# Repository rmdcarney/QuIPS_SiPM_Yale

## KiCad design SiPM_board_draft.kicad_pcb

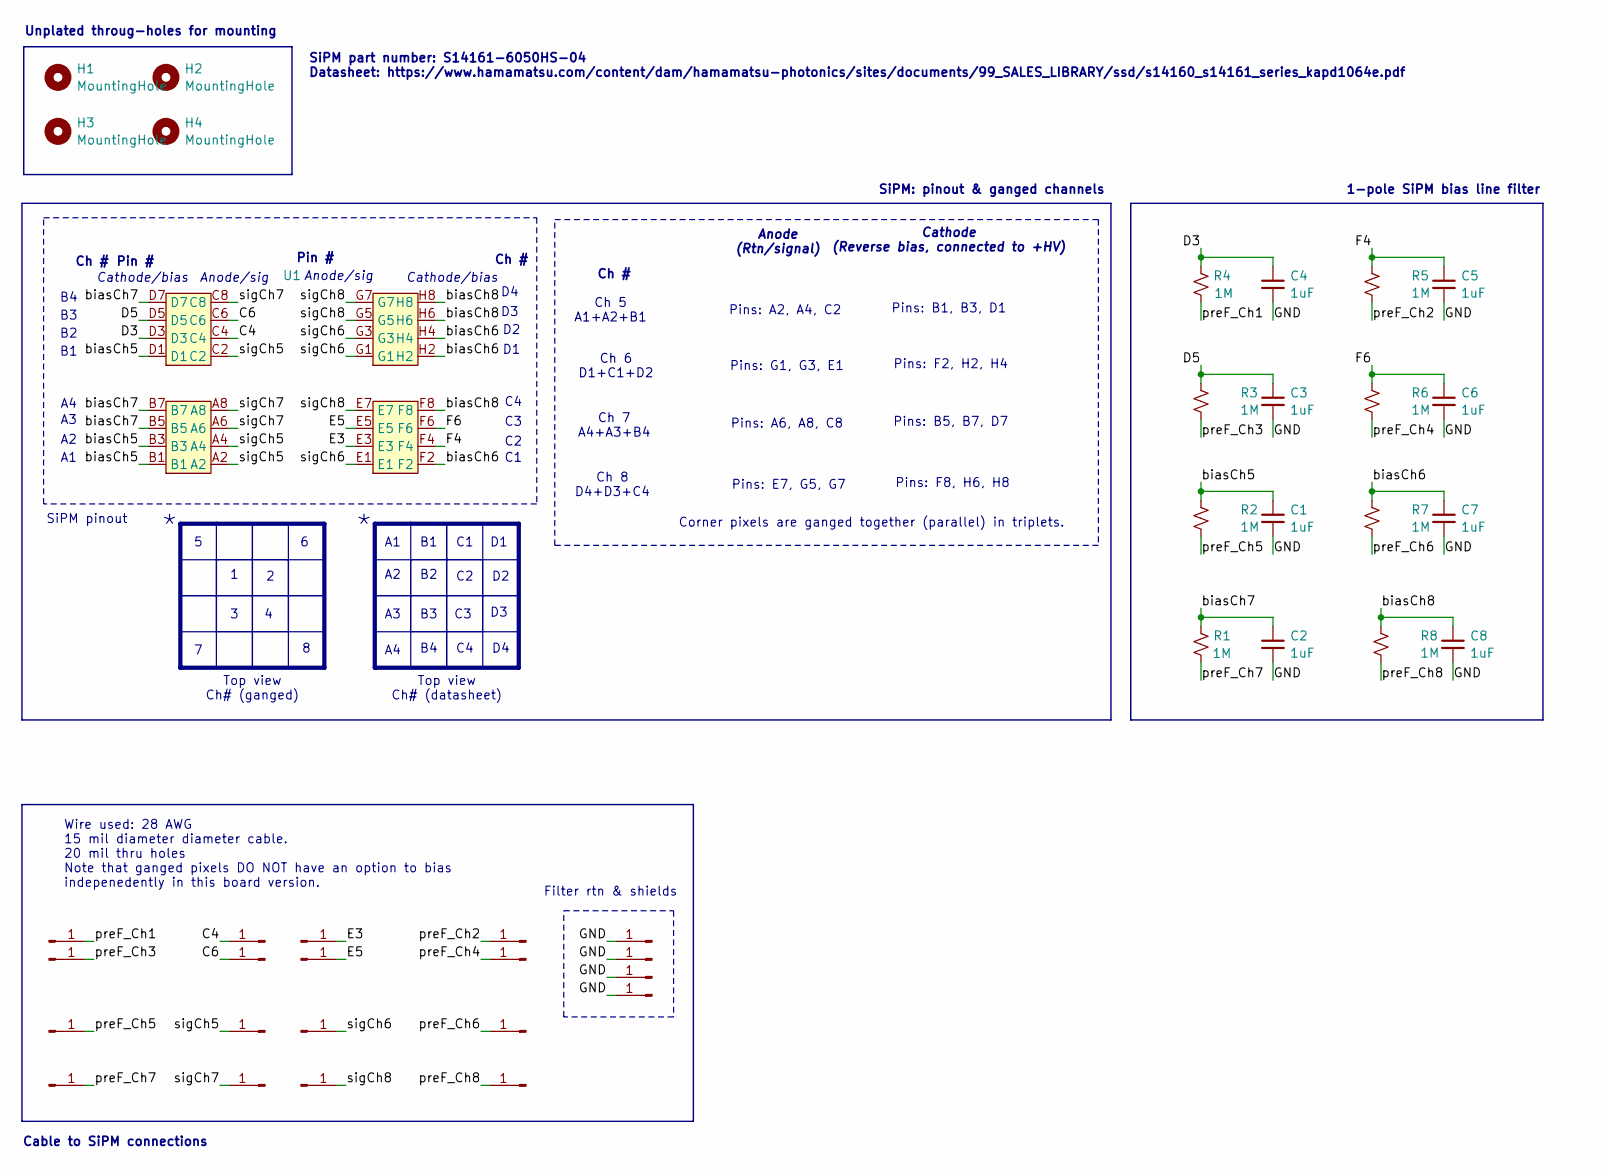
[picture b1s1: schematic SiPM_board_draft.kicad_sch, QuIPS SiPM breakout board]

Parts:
C1, C2, C3, C4, C5, C6, C7, C8: 1uF; C_0805_2012Metric
H1, H2, H3, H4: MountingHole; MountingHole_3.5mm
J1, J2, J3, J4, J5, J7, J8, J10, J11, J12, J13, J16, J18, J19, J21, J24, J26, J27, J29, J32: Conn_01x01_Pin; SolderWire-0.15sqmm_1x01_D0.5mm_OD1.5mm
R1, R2, R3, R4, R5, R6, R7, R8: 1M; R_0402_1005Metric
U1: S14161-6050HS-04_landing

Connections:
/C4: J19.1, U1.C4
/C6: J18.1, U1.C6
/D3: C4.1, R4.1, U1.D3
/D5: C3.1, R3.1, U1.D5
/E3: J10.1, U1.E3
/E5: J11.1, U1.E5
/F4: C5.1, R5.1, U1.F4
/F6: C6.1, R6.1, U1.F6
/GND: C1.2, C2.2, C3.2, C4.2, C5.2, C6.2, C7.2, C8.2, J1.1, J4.1, J7.1, J12.1
/biasCh5: C1.1, R2.1, U1.B1, U1.B3, U1.D1
/biasCh6: C7.1, R7.1, U1.F2, U1.H2, U1.H4
/biasCh7: C2.1, R1.1, U1.B5, U1.B7, U1.D7
/biasCh8: C8.1, R8.1, U1.F8, U1.H6, U1.H8
/preF_Ch1: J2.1, R4.2
/preF_Ch2: J27.1, R5.2
/preF_Ch3: J3.1, R3.2
/preF_Ch4: J26.1, R6.2
/preF_Ch5: J5.1, R2.2
/preF_Ch6: J32.1, R7.2
/preF_Ch7: J8.1, R1.2
/preF_Ch8: J29.1, R8.2
/sigCh5: J24.1, U1.A2, U1.A4, U1.C2
/sigCh6: J13.1, U1.E1, U1.G1, U1.G3
/sigCh7: J21.1, U1.A6, U1.A8, U1.C8
/sigCh8: J16.1, U1.E7, U1.G5, U1.G7

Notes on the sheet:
Top view Ch# (datasheet)
Pins: G1, G3, E1
Cable to SiPM connections
Pins: A6, A8, C8
Anode (Rtn/signal)
Anode/sig
Cathode (Reverse bias, connected to +HV)
Pins: F8, H6, H8
Ch #
1-pole SiPM bias line filter
Pins: B5, B7, D7
Unplated throug-holes for mounting
Pins: A2, A4, C2
Corner pixels are ganged together (parallel) in triplets.
Cathode/bias
SiPM part number: S14161-6050HS-04 Datasheet: https://www.hamamatsu.com/content/dam/hamamatsu-photonics/sites/documents/99_SALES_LIBRARY/ssd/s14160_s14161_series_kapd1064e.pdf
Ch 5 A1+A2+B1
Wire used: 28 AWG 15 mil diameter diameter cable. 20 mil thru holes Note that ganged pixels DO NOT have an option to bias indepenedently in this board version.
Pin #
Ch 6 D1+C1+D2
SiPM pinout
Pins: F2, H2, H4
Pins: B1, B3, D1
Ch 8 D4+D3+C4
SiPM: pinout & ganged channels
Top view Ch# (ganged)
Ch 7 A4+A3+B4
Filter rtn & shields
Pins: E7, G5, G7

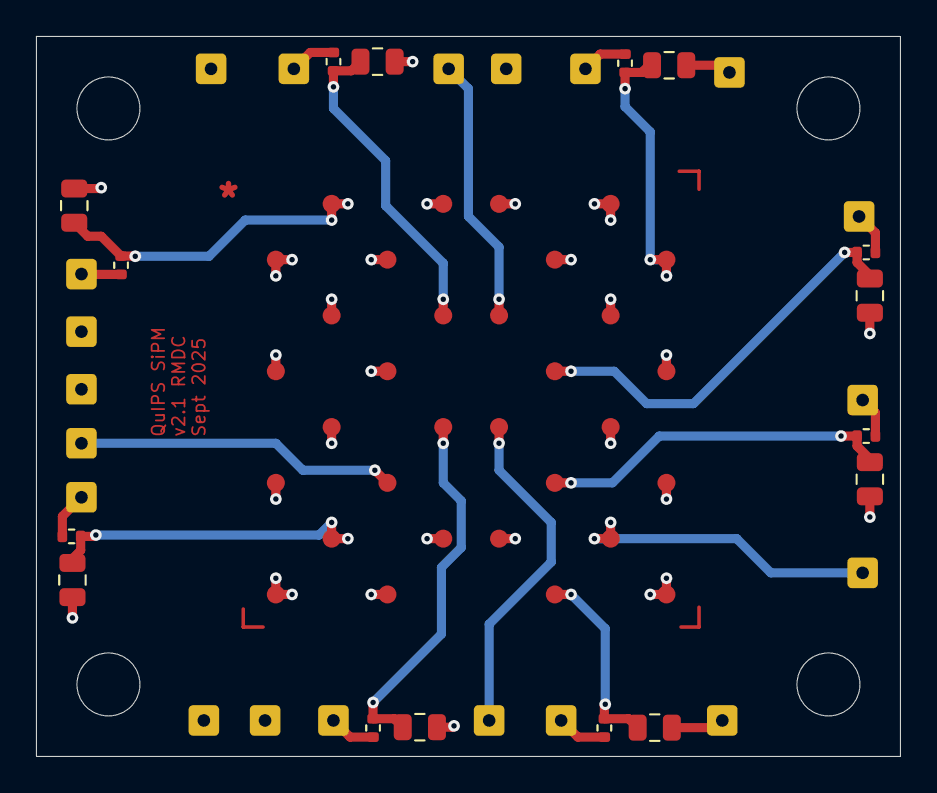
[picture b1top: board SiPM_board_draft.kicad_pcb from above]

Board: 4 copper layers, 48.0 x 40.0 mm, 41 parts (0 on the bottom side), 25 nets.

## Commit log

2025-07-14 First floorplan, no traces, vias
2025-07-16 V1.0 submitted for fab
2025-07-16 V1.1 - Added 0.7 mm clearance to all nets just to make sure there's no breakdowns.
2025-08-07 Fabricated version 1.
2025-09-04 First draft of schematic for RC variant of board complete. Started placing with 0402 resistors and 1210 caps. Caps are really big. See if I can go smaller?
2025-09-09 Rough placement.
2025-09-10 Branching here to make a shared ground.
2025-09-11 Changed everything to a common ground. Got rid of the jumpers and just made common nets. Reduced the number of ground lines on the board to 4. Everything placed. Going to try routing.
2025-09-11 First draft of full layout with hard-ganged parallel channels, 4 layer, common ground.
2025-09-12 First draft of board v2.1. Made caps all 0806, should be good for either 4.7uF at 50V or 2.2uF at 100V. Either way, sufficient for this application. This was done to decrease the vertical footprint o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
